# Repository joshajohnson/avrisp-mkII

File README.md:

# AVRISP-MKII

AVRISP-MKII clone, in a small form factor with USB Type C connector. 

## BUGS
- HWB does not appear to put the board into DFU.
- To flash the board, RST on the ISP header needs to be connected to RST on the MCU, and disconnected after.

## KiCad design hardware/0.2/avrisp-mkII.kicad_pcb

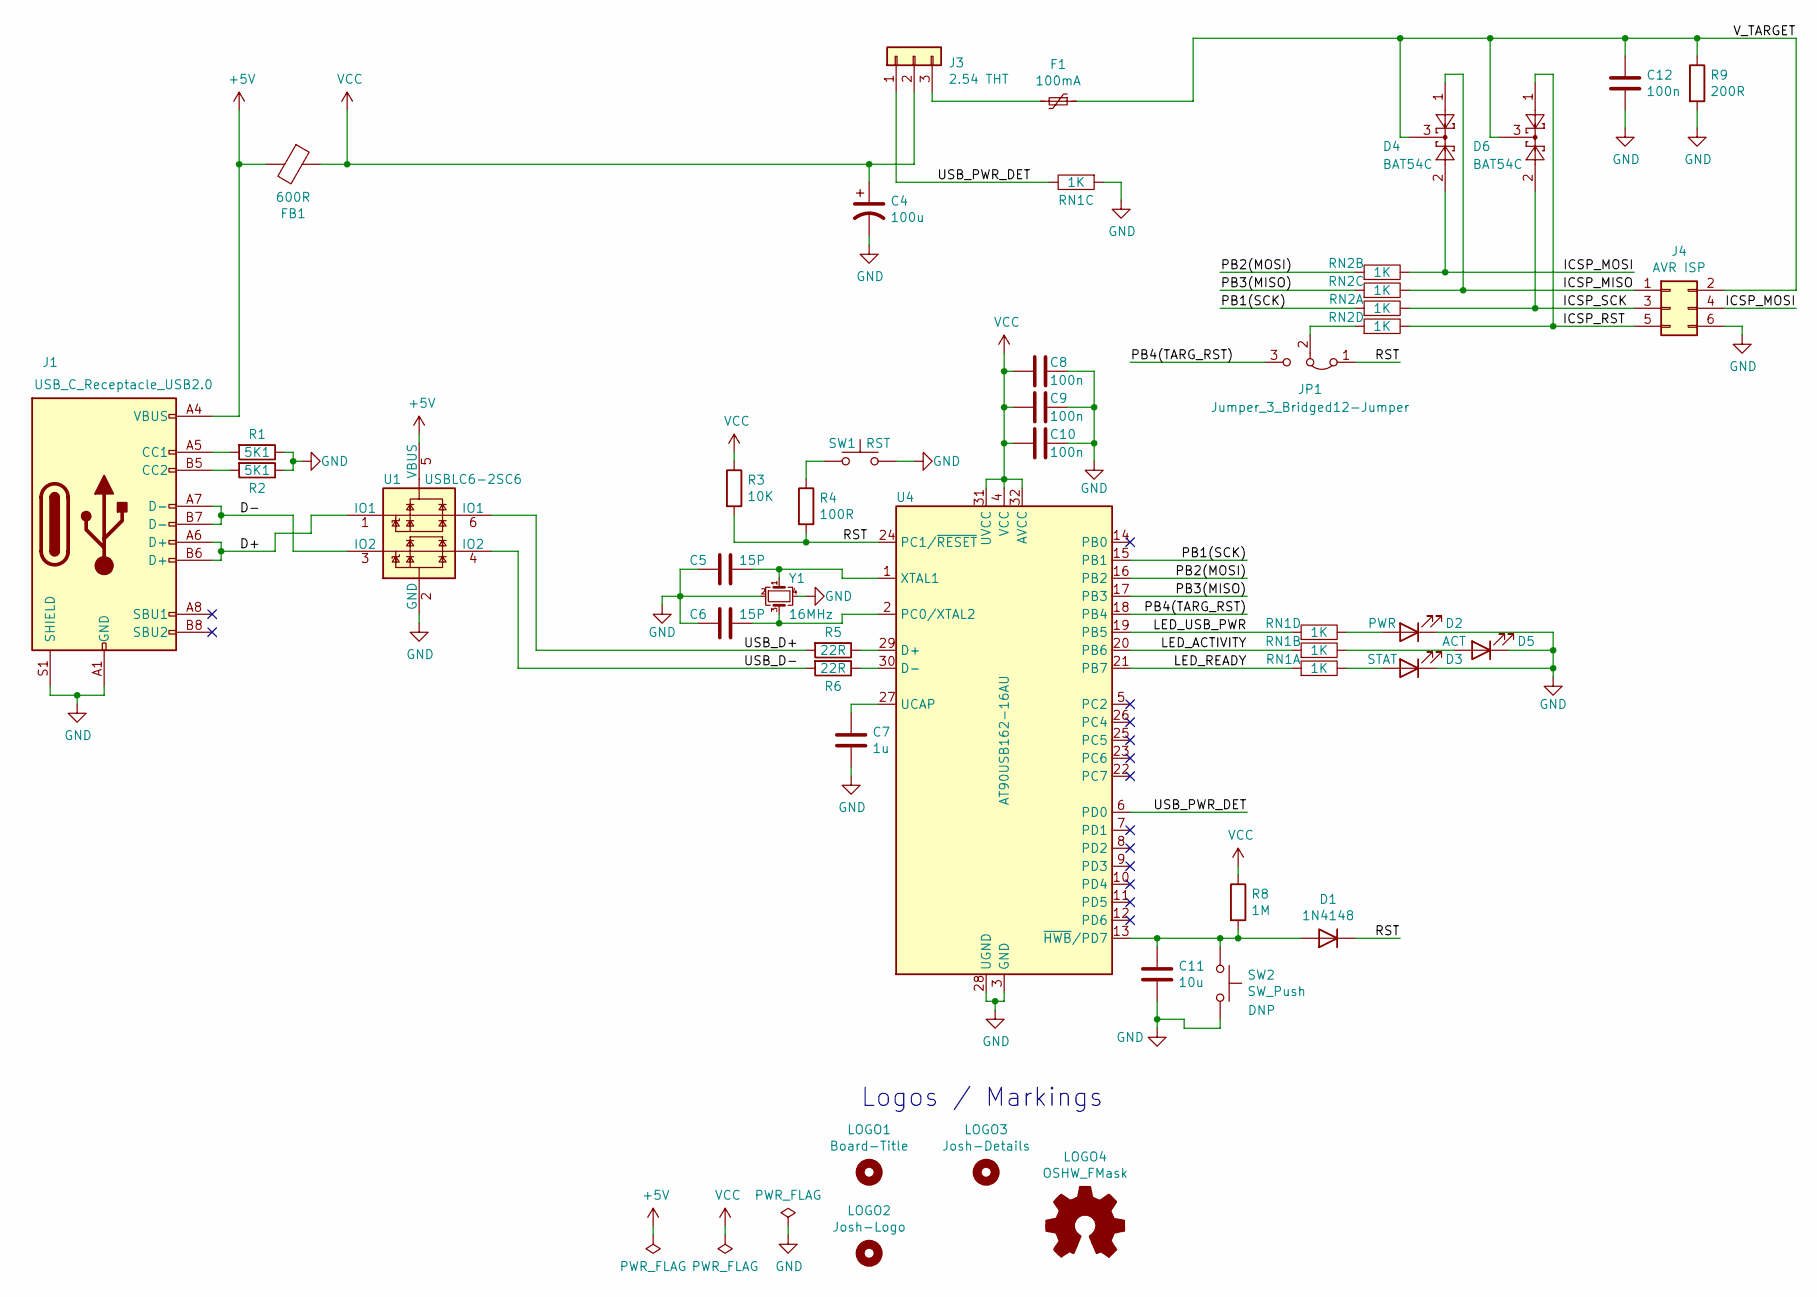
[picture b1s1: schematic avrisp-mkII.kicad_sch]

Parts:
C4: 100u; CP_EIA-3216-10_Kemet-I
C5, C6: 15P; C_0603_1608Metric
C7: 1u; C_0603_1608Metric
C8, C9, C10, C12: 100n; C_0603_1608Metric
C11: 10u; C_0603_1608Metric
D1: 1N4148; D_SOD-323
D2: PWR; LED_0603_1608Metric
D3: STAT; LED_0603_1608Metric
D4, D6: BAT54C; SOT-23
D5: ACT; LED_0603_1608Metric
F1: 100mA; Fuse_0805_2012Metric
FB1: 600R; Ferrite_Bead_0603
J1: USB_C_Receptacle_USB2.0; USB_C_U262-161N-4BVC11
J3: 2.54 THT; PinHeader_1x03_P2.54mm_Vertical
J4: AVR ISP; IDC-Header_2x03_P2.54mm_Vertical
JP1: Jumper_3_Bridged12-Jumper; SolderJumper-3_P1.3mm_Open_Pad1.0x1.5mm
LOGO1: Board-Title; board-title
LOGO2: Josh-Logo; josh-johnson-logo-8_6x1_5
LOGO3: Josh-Details; josh-details
LOGO4: OSHW_FMask; OSHW_Logo_3.6x3.6_F.Mask
R1, R2: 5K1; R_0603_1608Metric
R3: 10K; R_0603_1608Metric
R4: 100R; R_0603_1608Metric
R5, R6: 22R; R_0603_1608Metric
R8: 1M; R_0603_1608Metric
R9: 200R; R_0603_1608Metric
RN1, RN2: 1K; R_Array_Convex_4x0603
SW1: RST; Panasonic_EVQPUL_EVQPUC
SW2: SW_Push; Panasonic_EVQPUL_EVQPUC
U1: USBLC6-2SC6; SOT-23-6
U4: AT90USB162-16AU; TQFP-32_7x7mm_P0.8mm
Y1: 16MHz; Crystal_SMD_3225-4Pin_3.2x2.5mm

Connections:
+5V: FB1.2, J1.A4 (VBUS), J1.A9 (VBUS), J1.B4 (VBUS), J1.B9 (VBUS), U1.5 (VBUS)
/D+: J1.A6 (D+), J1.B6 (D+), U1.1 (IO1)
/D-: J1.A7 (D-), J1.B7 (D-), U1.3 (IO2)
/ICSP_MISO: D4.1, J4.1, RN2.7
/ICSP_MOSI: D4.2, J4.4, RN2.6
/ICSP_RST: D6.1, J4.5, RN2.8
/ICSP_SCK: D6.2, J4.3, RN2.5
/LED_ACTIVITY: RN1.3, U4.20 (PB6)
/LED_READY: RN1.4, U4.21 (PB7)
/LED_USB_PWR: RN1.1, U4.19 (PB5)
/PB1(SCK): RN2.4, U4.15 (PB1)
/PB2(MOSI): RN2.3, U4.16 (PB2)
/PB3(MISO): RN2.2, U4.17 (PB3)
/PB4(TARG_RST): JP1.3 (B), U4.18 (PB4)
/RST: D1.1 (K), JP1.1 (A), R3.2, R4.2, U4.24 (PC1/~RESET)
/USB_D+: R5.2, U1.6 (IO1)
/USB_D-: R6.2, U1.4 (IO2)
/USB_PWR_DET: J3.1, RN1.7, U4.6 (PD0)
/V_TARGET: C12.1, D4.3, D6.3, F1.1, J4.2, R9.1
GND: C4.2, C5.2, C6.2, C7.2, C8.1, C9.1, C10.1, C11.2, C12.2, D2.1 (K), D3.1 (K), D5.1 (K), J1.A1 (GND), J1.A12 (GND), J1.B1 (GND), J1.B12 (GND), J1.S1 (SHIELD), J4.6, R1.1, R2.1, R9.2, RN1.2, SW1.2, SW2.2, U1.2 (GND), U4.3 (GND), U4.28 (UGND), Y1.2, Y1.4
unnamed: C5.1, U4.1 (XTAL1), Y1.1
unnamed: C6.1, U4.2 (PC0/XTAL2), Y1.3
unnamed: C7.1, U4.27 (UCAP)
unnamed: C11.1, D1.2 (A), R8.2, SW2.1, U4.13 (~HWB~/PD7)
unnamed: D2.2 (A), RN1.8
unnamed: D3.2 (A), RN1.5
unnamed: D5.2 (A), RN1.6
unnamed: F1.2, J3.3
unnamed: J1.A5 (CC1), R1.2
unnamed: J1.B5 (CC2), R2.2
unnamed: JP1.2 (C), RN2.1
unnamed: R4.1, SW1.1
unnamed: R5.1, U4.29 (D+)
unnamed: R6.1, U4.30 (D-)
VCC: C4.1, C8.2, C9.2, C10.2, FB1.1, J3.2, R3.1, R8.1, U4.4 (VCC), U4.31 (UVCC), U4.32 (AVCC)

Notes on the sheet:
Logos / Markings

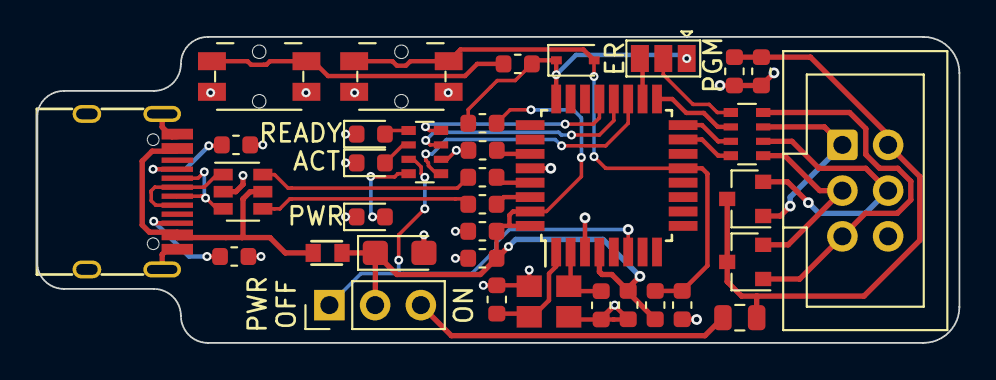
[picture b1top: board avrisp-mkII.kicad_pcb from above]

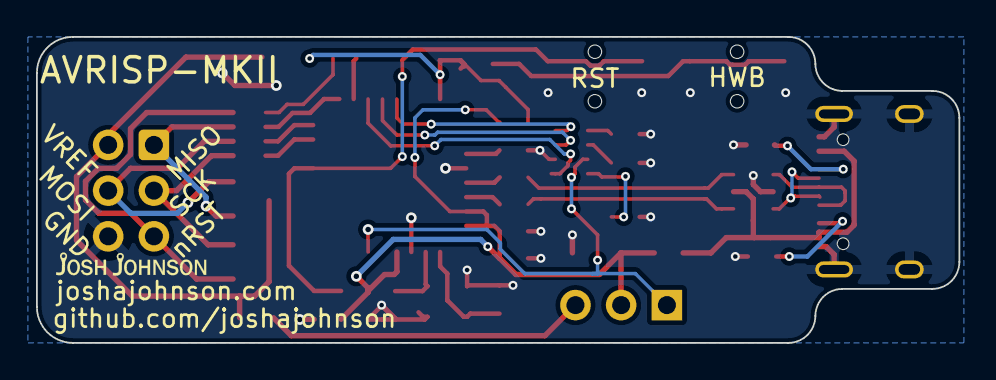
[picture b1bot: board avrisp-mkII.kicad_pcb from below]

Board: 2 copper layers, 51.2 x 17.0 mm, 40 parts (4 on the bottom side), 35 nets.

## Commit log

2020-05-24 schematic done
2020-05-24 layout done
2020-05-24 adding silk
2020-11-20 v0.2 initial layout done
